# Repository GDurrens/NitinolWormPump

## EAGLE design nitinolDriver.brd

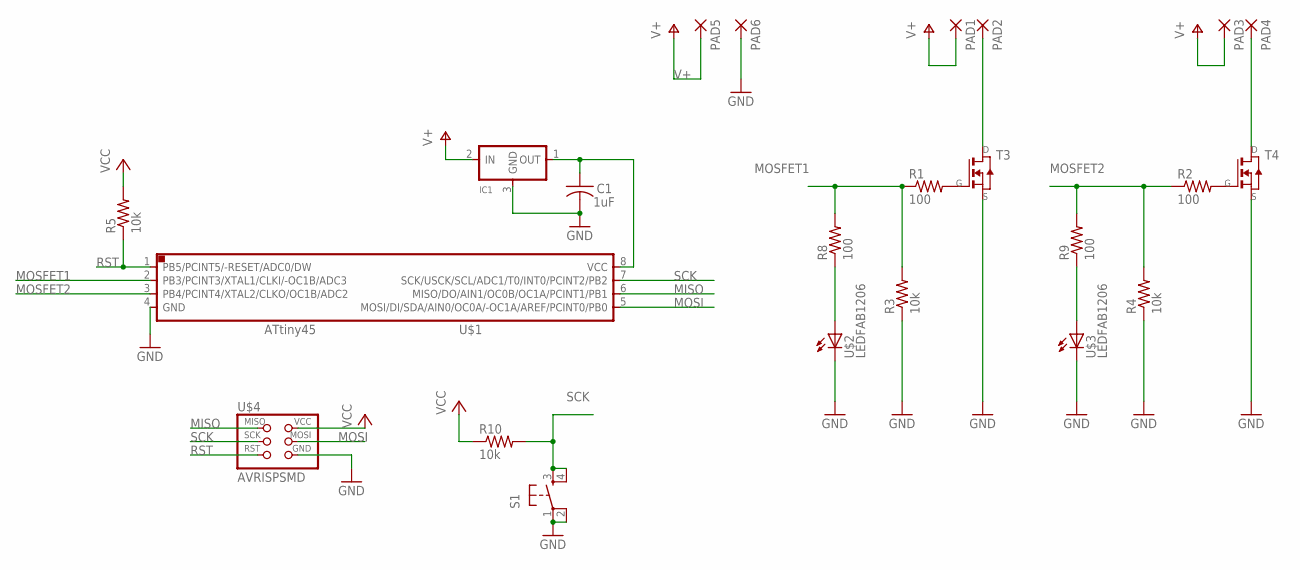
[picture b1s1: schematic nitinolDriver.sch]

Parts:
C1: 1uF; C1206FAB
IC1: REGULATORSOT23; SOT23
PAD1, PAD2, PAD3, PAD4, PAD5, PAD6: 2,15/1,0
R1, R2, R8, R9: 100; R1206FAB
R3, R4, R5, R10: 10k; R1206FAB
S1: 6MM_SWITCH6MM_SWITCH; 6MM_SWITCH
T3, T4: NMOSFETTO252; TO252
U$1: ATTINY45SI; SOIC8
U$2, U$3: LEDFAB1206; LED1206FAB
U$4: AVRISPSMD; 2X03SMD

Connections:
GND: C1.2, IC1.3 (GND), PAD6.1, R3.1, R4.1, S1.1, S1.2 (P1), T3.2 (S), T4.2 (S), U$1.4 (GND), U$2.2 (C), U$3.2 (C), U$4.6 (GND)
MISO: U$1.6 (MISO/DO/AIN1/OC0B/OC1A/PCINT1/PB1), U$4.1 (MISO)
MOSFET1: R1.1, R3.2, R8.2, U$1.2 (PB3/PCINT3/XTAL1/CLKI/-OC1B/ADC3)
MOSFET2: R2.1, R4.2, R9.2, U$1.3 (PB4/PCINT4/XTAL2/CLKO/OC1B/ADC2)
MOSI: U$1.5 (MOSI/DI/SDA/AIN0/OC0A/-OC1A/AREF/PCINT0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), U$4.4 (MOSI)
unnamed: R2.2, T4.1 (G)
unnamed: R1.2, T3.1 (G)
unnamed: R8.1, U$2.1 (A)
unnamed: R9.1, U$3.1 (A)
unnamed: PAD4.1, T4.3 (D)
unnamed: PAD2.1, T3.3 (D)
RST: R5.1, U$1.1 (PB5/PCINT5/-RESET/ADC0/DW), U$4.5 (RST)
SCK: R10.2, S1.3 (S), S1.4 (S1), U$1.7 (SCK/USCK/SCL/ADC1/T0/INT0/PCINT2/PB2), U$4.3 (SCK)
V+: IC1.2 (IN), PAD1.1, PAD3.1, PAD5.1
VCC: C1.1, IC1.1 (OUT), R5.2, R10.1, U$1.8 (VCC), U$4.2 (VCC)

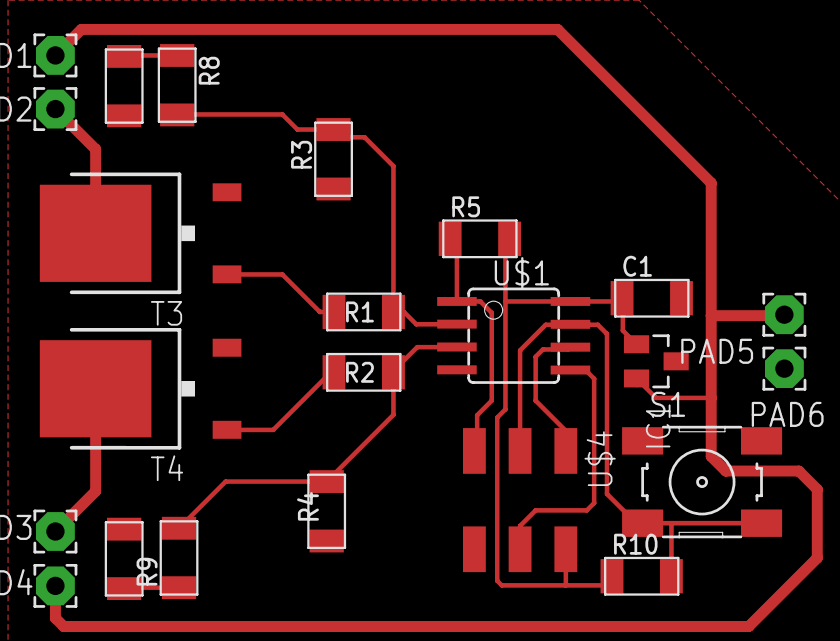
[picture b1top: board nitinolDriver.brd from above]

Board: 1 copper layer, 23 parts (0 on the bottom side), 15 nets.

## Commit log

2016-05-05 DualNitinol mosfet driver
2016-05-05 first basic program for the MCU
2016-05-10 changed to 16A NMOSFETs
